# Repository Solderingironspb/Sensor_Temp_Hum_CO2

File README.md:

# Sensor_Temp_Hum_CO2
## Датчик температуры, влажности и углекислого газа. Подключается к системе умного дома по MQTT.

**Это опытный образец. Датчик температуры пришлось отпилить от текстолита и вынести наружу, так как ESP8266 подогревала его, что влияло на точность. 
Проект больше личный, чем массовый. Но если хотите собрать это, то обращайтесь - помогу. Код написан на CMSIS. МК STM32F103C6T6/STM32F103C8T6**
### Плата двухсторонняя. Сделана в домашних условиях. Выполнена сверловка отверстий и обрезка контура на ЧПУ. Далее изготовление шло при помощи пленочного фоторезиста.

### Сам корпус куплен на алиэкспресс. На 3D принтере напечатал кожух для внешнего датчика температуры.

### Интеграция данных по MQTT в Home Assistant

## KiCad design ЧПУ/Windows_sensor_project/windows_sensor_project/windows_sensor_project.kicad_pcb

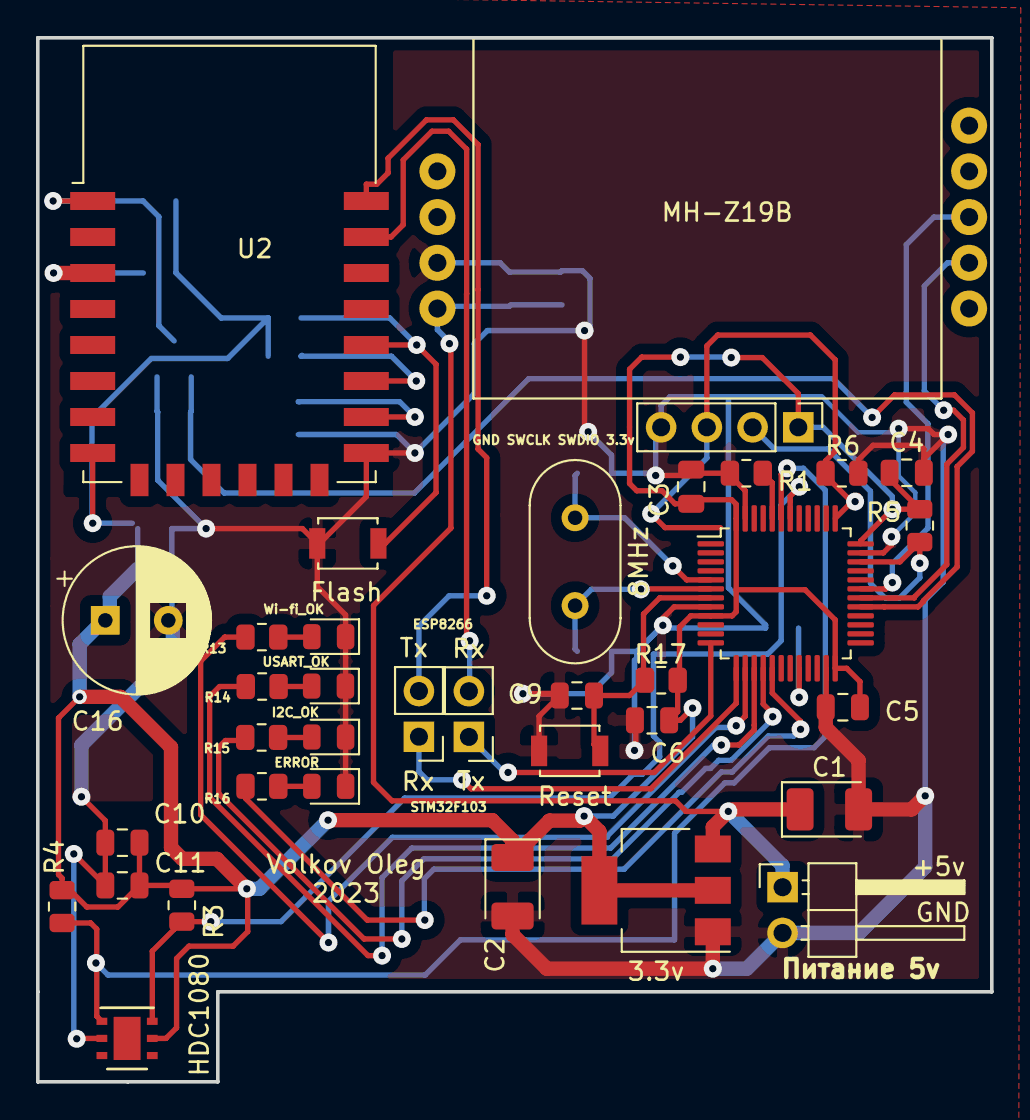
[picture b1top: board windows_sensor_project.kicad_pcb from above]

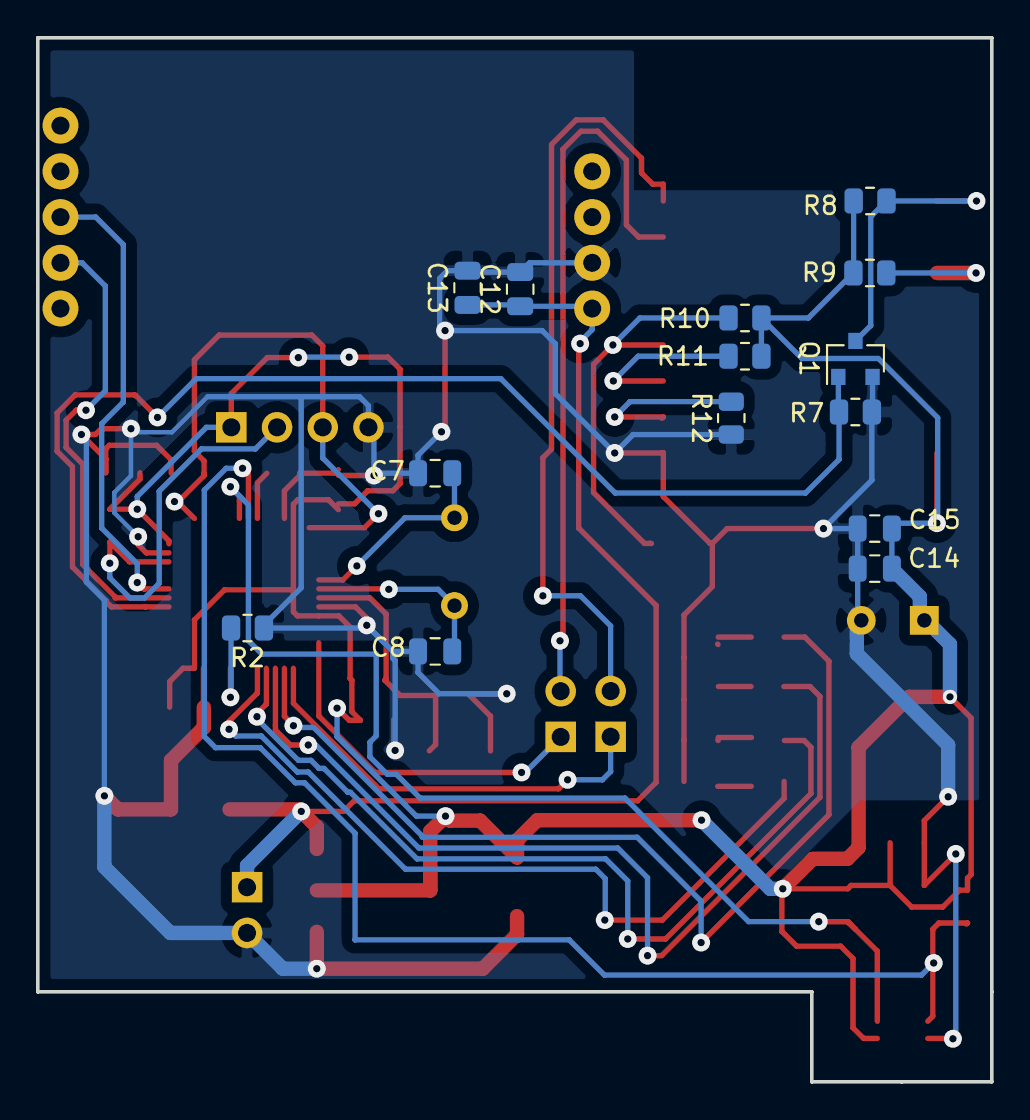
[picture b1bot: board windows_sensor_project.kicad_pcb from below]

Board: 2 copper layers, 53.0 x 58.0 mm, 50 parts (14 on the bottom side), 32 nets.

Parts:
3.3v: AMS1117-3.3; SOT-223-3_TabPin2
8MHz: 8MHz; Crystal_HC49-U_Vertical
C1, C2: 47u; CP_EIA-3528-21_Kemet-B_Pad1.50x2.35mm_HandSolder
C3, C4, C5, C6, C9, C11, C12, C15: 0.1u; C_0805_2012Metric
C7, C8: 30pF; C_0805_2012Metric
C10, C13, C14: 10u; C_0805_2012Metric
C16: 100uF; CP_Radial_D8.0mm_P3.50mm
ERROR: LED; LED_0805_2012Metric
Flash: flash; SW_SPST_B3U-1000P
HDC1080: HDC1080; Texas_PWSON-N6
I2C_OK: LED; LED_0805_2012Metric
J1: Debug; PinHeader_1x04_P2.54mm_Vertical
J4: Питание; PinHeader_1x02_P2.54mm_Horizontal
Q1: IRLML0060; SOT-23
R1, R2, R5, R6, R8, R9, R10, R11, R12, R17: 10k; R_0805_2012Metric
R3, R4, R7: 4.7k; R_0805_2012Metric
R13, R14, R15, R16: 1k; R_0805_2012Metric
Reset: Reset; SW_SPST_B3U-1000P
Rx: Rx; PinHeader_1x02_P2.54mm_Vertical
Tx: Conn_01x02_Male; PinHeader_1x02_P2.54mm_Vertical
U1: STM32F103C8Tx; LQFP-48_7x7mm_P0.5mm
U2: ESP-12E
U4: MH-Z19B; MH-Z19B-FOOT
USART_OK: LED; LED_0805_2012Metric
Wi-fi_OK: LED; LED_0805_2012Metric

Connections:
3.3v: 3.3v.2, C2.1, C3.1, C4.1, C5.1, C6.1, C10.1, C11.1, C14.2, C15.1, C16.1, HDC1080.5, J1.1, R3.1, R4.1, R5.1, R8.2, R9.2, R10.1, R11.2, R17.1, U1.9, U1.24, U1.36, U1.48, U2.8
5v: 3.3v.3, C1.1, C12.1, C13.1, J4.1, U4.VIN
BOOT0: R1.2, U1.44
BOOT1: R2.2, U1.20
ESP8266_Reset: Q1.1, R7.1, U1.29
ESP_UART_Rx: Tx.2, U2.21
ESP_UART_Tx: Rx.2, U2.22
Error: R16.2, U1.17
GND: 3.3v.1, C1.2, C2.2, C3.2, C4.2, C5.2, C6.2, C7.2, C8.2, C9.1, C10.2, C11.2, C12.2, C13.2, C14.1, C15.2, C16.2, ERROR.1, Flash.1, HDC1080.2, I2C_OK.1, J1.4, J4.2, Q1.2, R1.1, R2.1, R6.2, R7.2, R12.1, Reset.1, U1.8, U1.23, U1.35, U1.47, U2.15, U4.GND, USART_OK.1, Wi-fi_OK.1
I2C1_SCL: HDC1080.6, R3.2, U1.42
I2C1_SDA: HDC1080.1, R4.2, U1.43
I2C_ok: R15.2, U1.16
NRST: C9.2, R17.2, Reset.2, U1.7
unnamed: R13.1, Wi-fi_OK.2
unnamed: R14.1, USART_OK.2
unnamed: I2C_OK.2, R15.1
unnamed: ERROR.2, R16.1
unnamed: Flash.2, R10.2, U2.18
unnamed: Q1.3, R8.1, U2.1
unnamed: R9.1, U2.3
unnamed: R11.1, U2.17
unnamed: R12.2, U2.16
PA13: J1.2, R5.2, U1.34
PA14: J1.3, R6.1, U1.37
PD0: 8MHz.1, C7.1, U1.5
PD1: 8MHz.2, C8.1, U1.6
USART1_Rx: U1.31, U4.TX
USART1_Tx: U1.30, U4.RX
USART1_ok: R14.2, U1.15
USART2_Rx: Rx.1, U1.13
USART2_Tx: Tx.1, U1.12
WiFi_ok: R13.2, U1.14

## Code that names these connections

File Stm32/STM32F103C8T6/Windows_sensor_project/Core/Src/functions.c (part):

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void GPIO_Init(void) {
	RCC->APB2ENR = RCC_APB2ENR_IOPAEN; //Запуск тактирование порта A
	/*--------------------Настройка светодиодной индикации--------------------*/
	// PA4-Wifi_OK
	MODIFY_REG(GPIOA->CRL, GPIO_CRL_MODE4, 0b10 << GPIO_CRL_MODE4_Pos);
	MODIFY_REG(GPIOA->CRL, GPIO_CRL_CNF4, 0b00 << GPIO_CRL_CNF4_Pos);
	// PA5-USART1_OK
	MODIFY_REG(GPIOA->CRL, GPIO_CRL_MODE5, 0b10 << GPIO_CRL_MODE5_Pos);
	MODIFY_REG(GPIOA->CRL, GPIO_CRL_CNF5, 0b00 << GPIO_CRL_CNF5_Pos);
	// PA6-I2C1_OK
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	// PA7-Error
	MODIFY_REG(GPIOA->CRL, GPIO_CRL_MODE7, 0b10 << GPIO_CRL_MODE7_Pos);
	MODIFY_REG(GPIOA->CRL, GPIO_CRL_CNF7, 0b00 << GPIO_CRL_CNF7_Pos);
	// PA8-ESP8266_Reset
	MODIFY_REG(GPIOA->CRH, GPIO_CRH_MODE8, 0b10 << GPIO_CRH_MODE8_Pos);
	MODIFY_REG(GPIOA->CRH, GPIO_CRH_CNF8, 0b00 << GPIO_CRH_CNF8_Pos);
	/*--------------------Настройка светодиодной индикации--------------------*/
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
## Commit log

2023-01-11 add project Sensor_Temp_Hum_CO2
2023-08-11 Перереаботал проект. Использовал FreeRTOS
2023-08-16 Стабильная версия
